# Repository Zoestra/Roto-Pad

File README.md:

# Roto-Pad
 Macropad with Rotories

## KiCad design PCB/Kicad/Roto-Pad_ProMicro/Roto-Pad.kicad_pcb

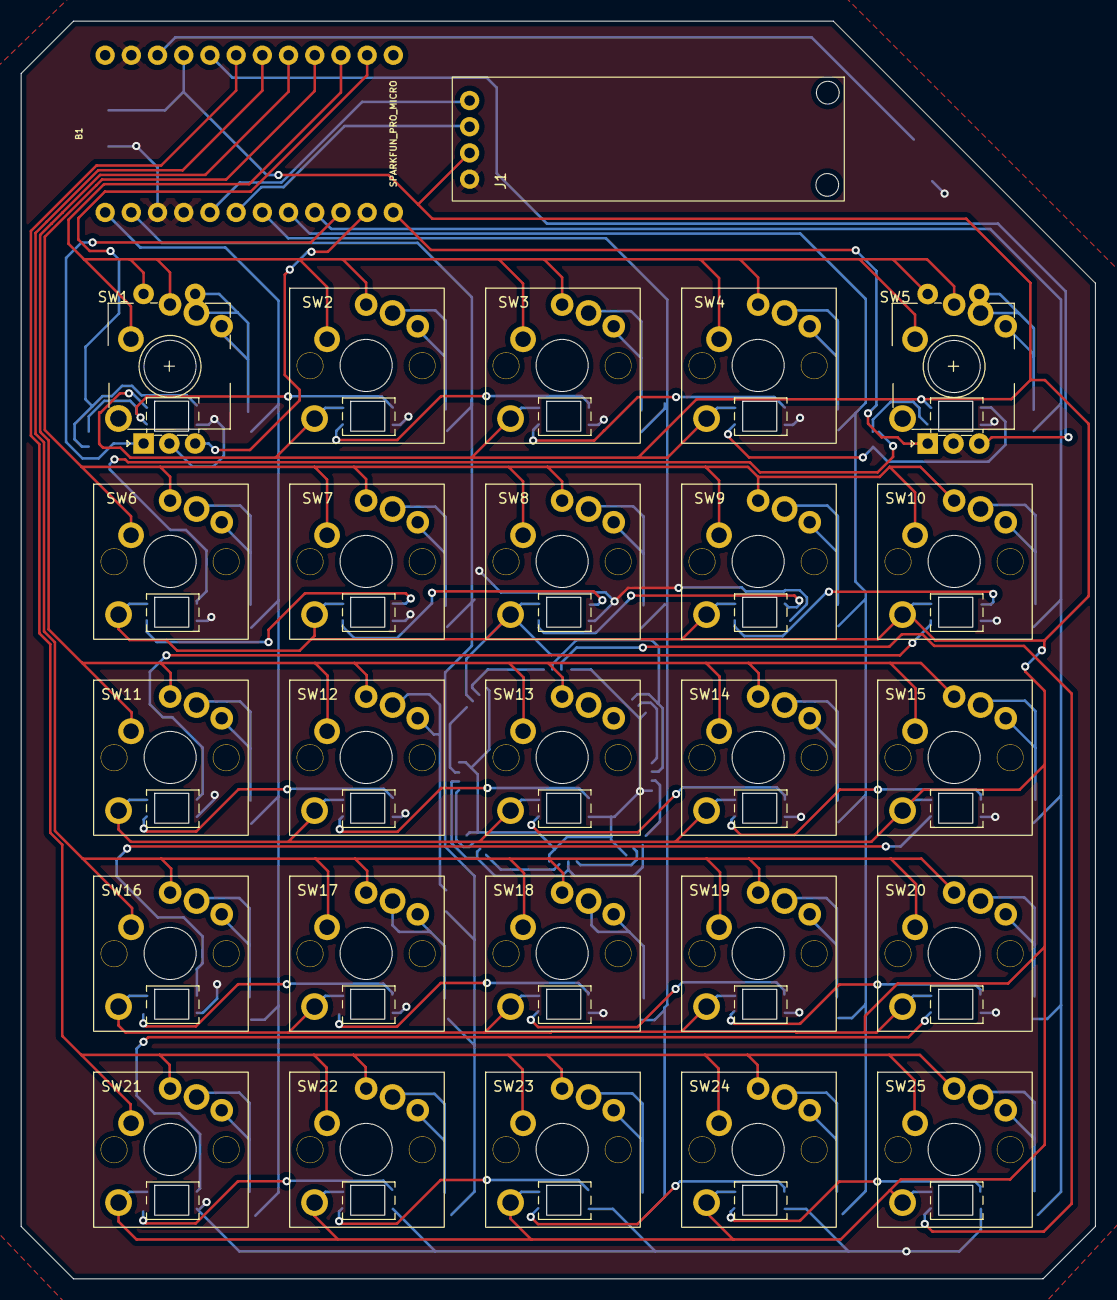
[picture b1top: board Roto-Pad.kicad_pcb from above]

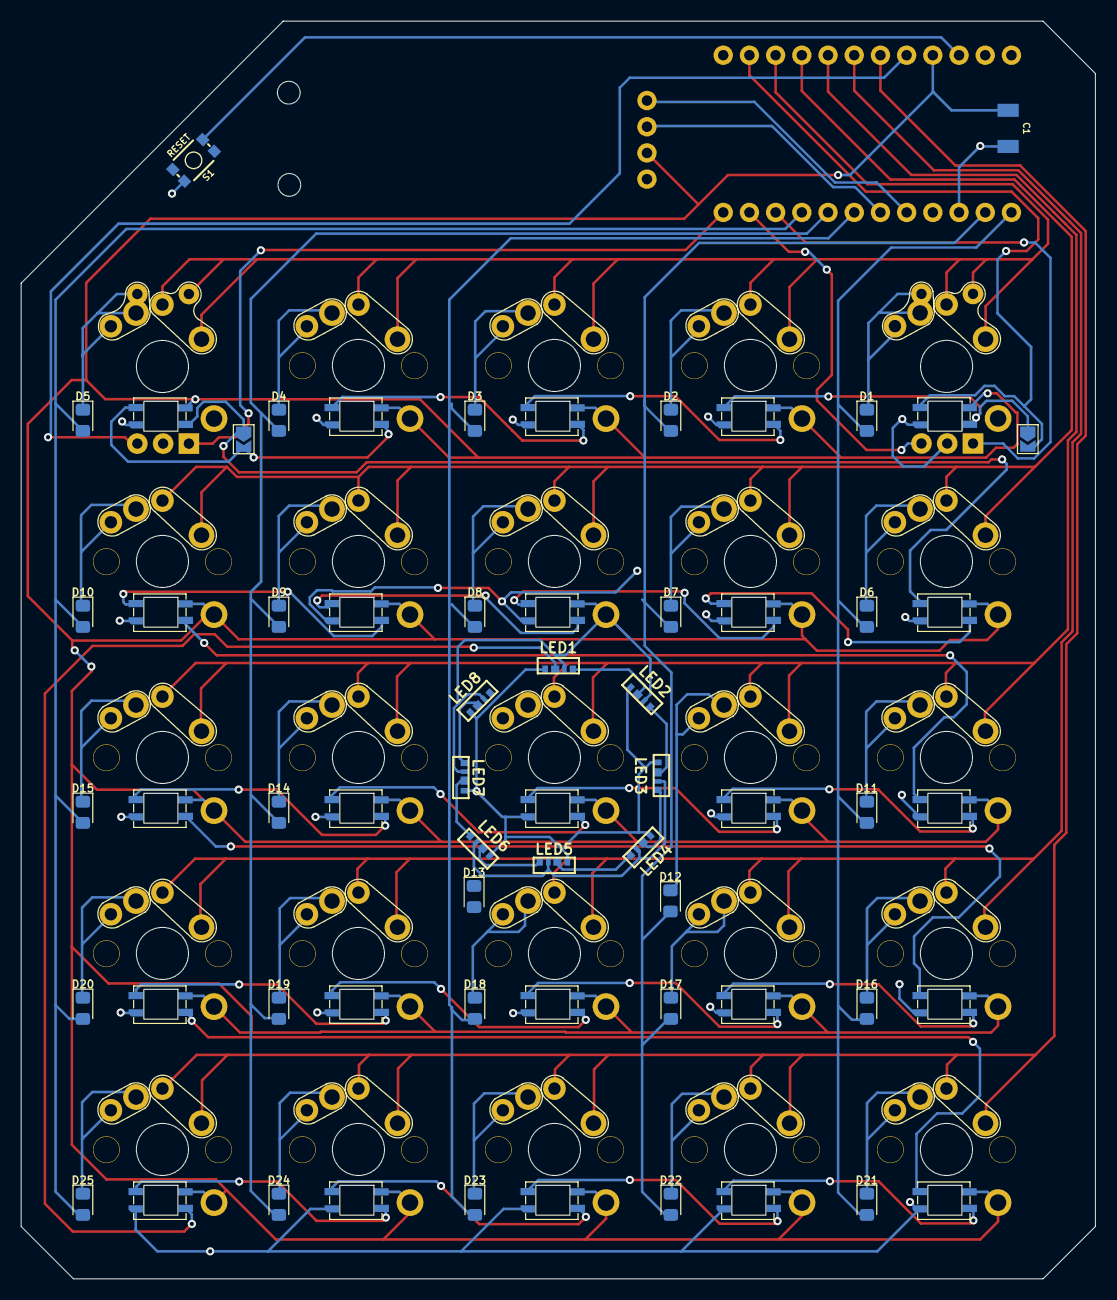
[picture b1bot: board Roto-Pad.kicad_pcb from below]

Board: 2 copper layers, 104.1 x 121.9 mm, 62 parts (35 on the bottom side), 77 nets.

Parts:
B1: SPARKFUN_PRO_MICRO
C1: C_Polarized_1000uf; 1210
D1, D2, D3, D4, D5, D6, D7, D8, D9, D10, D11, D12, D13, D14, D15, D16, D17, D18, D19, D20, D21, D22, D23, D24, D25: DIODE-1N4148; D_0805_2012Metric_Pad1.15x1.40mm_HandSolder
J1: I2C_STANDARD_NO_SILK; TINY OLED I2C
LED1, LED2, LED3, LED4, LED5, LED6, LED7, LED8: LED_SK6812; WS2812B-4020
S1: RESET; TACTILE_SWITCH_SMD_4.6X2.8MM
SW1, SW5: RotarySwitchLedHybrid; xX_Super_Heckin_Valid_Rotary_MX_Kailh_Hybrid_UwU_Xx
SW2, SW3, SW4, SW6, SW7, SW8, SW9, SW10, SW11, SW12, SW13, SW14, SW15, SW16, SW17, SW18, SW19, SW20, SW21, SW22, SW23, SW24, SW25: HECKIN_LED_SWITCH; xX_Super_Heckin_Valid_MX_CHOC_SK6812MINIE_ONESIDE_KEYSWITCH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

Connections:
5V: B1.21 (VCC), C1.1, J1.VCC, LED1.3 (VDD), LED2.3 (VDD), LED3.3 (VDD), LED4.3 (VDD), LED5.3 (VDD), LED6.3 (VDD), LED7.3 (VDD), LED8.3 (VDD), SW1.3 (5v), SW2.3 (5v), SW3.3 (5v), SW4.3 (5v), SW5.3 (5v), SW6.3 (5v), SW7.3 (5v), SW8.3 (5v), SW9.3 (5v), SW10.3 (5v), SW11.3 (5v), SW12.3 (5v), SW13.3 (5v), SW14.3 (5v), SW15.3 (5v), SW16.3 (5v), SW17.3 (5v), SW18.3 (5v), SW19.3 (5v), SW20.3 (5v), SW21.3 (5v), SW22.3 (5v), SW23.3 (5v), SW24.3 (5v), SW25.3 (5v)
Col1: B1.2 (RXI), D2.C, D7.C, D12.C, D17.C, D22.C
Col 0: B1.1 (TXO), D1.C, D6.C, D11.C, D16.C, D21.C
Col 2: B1.7 (4), D3.C, D8.C, D13.C, D18.C, D23.C
Col 3: B1.8 (*5), D4.C, D9.C, D14.C, D19.C, D24.C
Col 4: B1.9 (*6), D5.C, D10.C, D15.C, D20.C, D25.C
Earth: B1.3 (GND), B1.4 (GND), B1.23 (GND), C1.2, J1.GND, LED1.1 (VSS), LED2.1 (VSS), LED3.1 (VSS), LED4.1 (VSS), LED5.1 (VSS), LED6.1 (VSS), LED7.1 (VSS), LED8.1 (VSS), S1.3, SW1.6 (GND), SW1.C, SW2.6 (GND), SW3.6 (GND), SW4.6 (GND), SW5.6 (GND), SW5.C, SW6.6 (GND), SW7.6 (GND), SW8.6 (GND), SW9.6 (GND), SW10.6 (GND), SW11.6 (GND), SW12.6 (GND), SW13.6 (GND), SW14.6 (GND), SW15.6 (GND), SW16.6 (GND), SW17.6 (GND), SW18.6 (GND), SW19.6 (GND), SW20.6 (GND), SW21.6 (GND), SW22.6 (GND), SW23.6 (GND), SW24.6 (GND), SW25.6 (GND)
LED CONTROL: B1.14 (11(MOSI)), SW1.5 (DIN)
Ledthru: LED1.2 (DIN), SW25.4 (DOUT)
Ledthru2: LED4.4 (DOUT), LED5.2 (DIN)
unnamed: B1.22 (RESET), S1.1
unnamed: D1.A, SW1.2 (Sw2)
unnamed: D2.A, SW2.2 (Sw2)
unnamed: D3.A, SW3.2 (Sw2)
unnamed: D4.A, SW4.2 (Sw2)
unnamed: D5.A, SW5.2 (Sw2)
unnamed: D6.A, SW6.2 (Sw2)
unnamed: D7.A, SW7.2 (Sw2)
unnamed: D8.A, SW8.2 (Sw2)
unnamed: D9.A, SW9.2 (Sw2)
unnamed: D10.A, SW10.2 (Sw2)
unnamed: D11.A, SW11.2 (Sw2)
unnamed: D12.A, SW12.2 (Sw2)
unnamed: D13.A, SW13.2 (Sw2)
unnamed: D14.A, SW14.2 (Sw2)
unnamed: D15.A, SW15.2 (Sw2)
unnamed: D16.A, SW16.2 (Sw2)
unnamed: D17.A, SW17.2 (Sw2)
unnamed: D18.A, SW18.2 (Sw2)
unnamed: D19.A, SW19.2 (Sw2)
unnamed: D20.A, SW20.2 (Sw2)
unnamed: D21.A, SW21.2 (Sw2)
unnamed: D22.A, SW22.2 (Sw2)
unnamed: D23.A, SW23.2 (Sw2)
unnamed: D24.A, SW24.2 (Sw2)
unnamed: D25.A, SW25.2 (Sw2)
unnamed: LED1.4 (DOUT), LED2.2 (DIN)
unnamed: LED2.4 (DOUT), LED3.2 (DIN)
unnamed: LED3.4 (DOUT), LED4.2 (DIN)
unnamed: LED5.4 (DOUT), LED6.2 (DIN)
unnamed: LED6.4 (DOUT), LED7.2 (DIN)
unnamed: LED7.4 (DOUT), LED8.2 (DIN)
unnamed: SW1.4 (DOUT), SW2.5 (DIN)
unnamed: SW2.4 (DOUT), SW3.5 (DIN)
unnamed: SW3.4 (DOUT), SW4.5 (DIN)
unnamed: SW4.4 (DOUT), SW5.5 (DIN)
unnamed: SW5.4 (DOUT), SW6.5 (DIN)
unnamed: SW6.4 (DOUT), SW7.5 (DIN)
unnamed: SW7.4 (DOUT), SW8.5 (DIN)
unnamed: SW8.4 (DOUT), SW9.5 (DIN)
unnamed: SW10.4 (DOUT), SW11.5 (DIN)
unnamed: SW9.4 (DOUT), SW10.5 (DIN)
unnamed: SW11.4 (DOUT), SW12.5 (DIN)
unnamed: SW12.4 (DOUT), SW13.5 (DIN)
unnamed: SW13.4 (DOUT), SW14.5 (DIN)
unnamed: SW14.4 (DOUT), SW15.5 (DIN)
unnamed: SW15.4 (DOUT), SW16.5 (DIN)
unnamed: SW16.4 (DOUT), SW17.5 (DIN)
unnamed: SW17.4 (DOUT), SW18.5 (DIN)
unnamed: SW18.4 (DOUT), SW19.5 (DIN)
unnamed: SW19.4 (DOUT), SW20.5 (DIN)
unnamed: SW20.4 (DOUT), SW21.5 (DIN)
unnamed: SW21.4 (DOUT), SW22.5 (DIN)
unnamed: SW22.4 (DOUT), SW23.5 (DIN)
unnamed: SW23.4 (DOUT), SW24.5 (DIN)
unnamed: SW24.4 (DOUT), SW25.5 (DIN)
Rot1 A: B1.10 (7), SW1.A
Rot1B: B1.11 (8), SW1.B
Rot2B: B1.20 (A3), SW5.B
Rot 2 A: B1.12 (*9), SW5.A
Row 0: B1.15 (12(MISO)), SW1.1 (Sw1), SW2.1 (Sw1), SW3.1 (Sw1), SW4.1 (Sw1), SW5.1 (Sw1)
Row 1: B1.16 (13(SCK)), SW6.1 (Sw1), SW7.1 (Sw1), SW8.1 (Sw1), SW9.1 (Sw1), SW10.1 (Sw1)
Row 2: B1.17 (A0), SW11.1 (Sw1), SW12.1 (Sw1), SW13.1 (Sw1), SW14.1 (Sw1), SW15.1 (Sw1)
Row 3: B1.18 (A1), SW16.1 (Sw1), SW17.1 (Sw1), SW18.1 (Sw1), SW19.1 (Sw1), SW20.1 (Sw1)
Row 4: B1.19 (A2), SW21.1 (Sw1), SW22.1 (Sw1), SW23.1 (Sw1), SW24.1 (Sw1), SW25.1 (Sw1)
SCL: B1.6 (*3), J1.SCL
SDA: B1.5 (2), J1.SDA

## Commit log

2022-07-13 Seeed 1st commit
    started seeed variant and reorganized folders
2022-07-14 seeed PCB completed
2022-07-25 seeed board changes
